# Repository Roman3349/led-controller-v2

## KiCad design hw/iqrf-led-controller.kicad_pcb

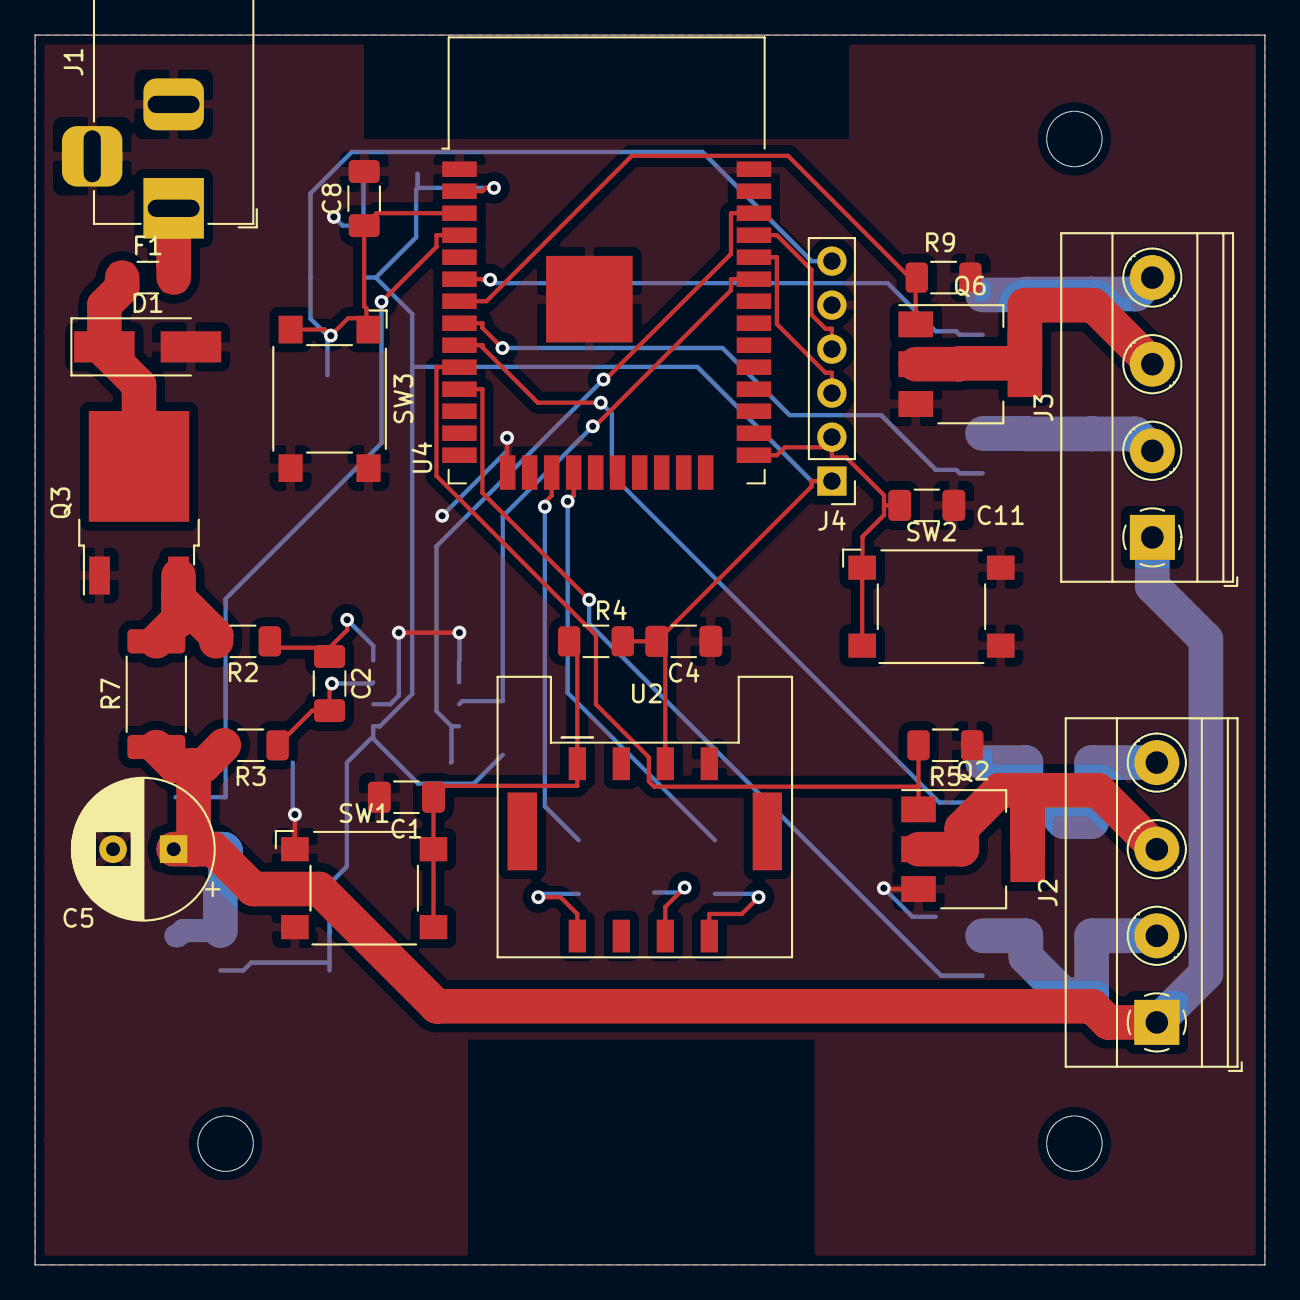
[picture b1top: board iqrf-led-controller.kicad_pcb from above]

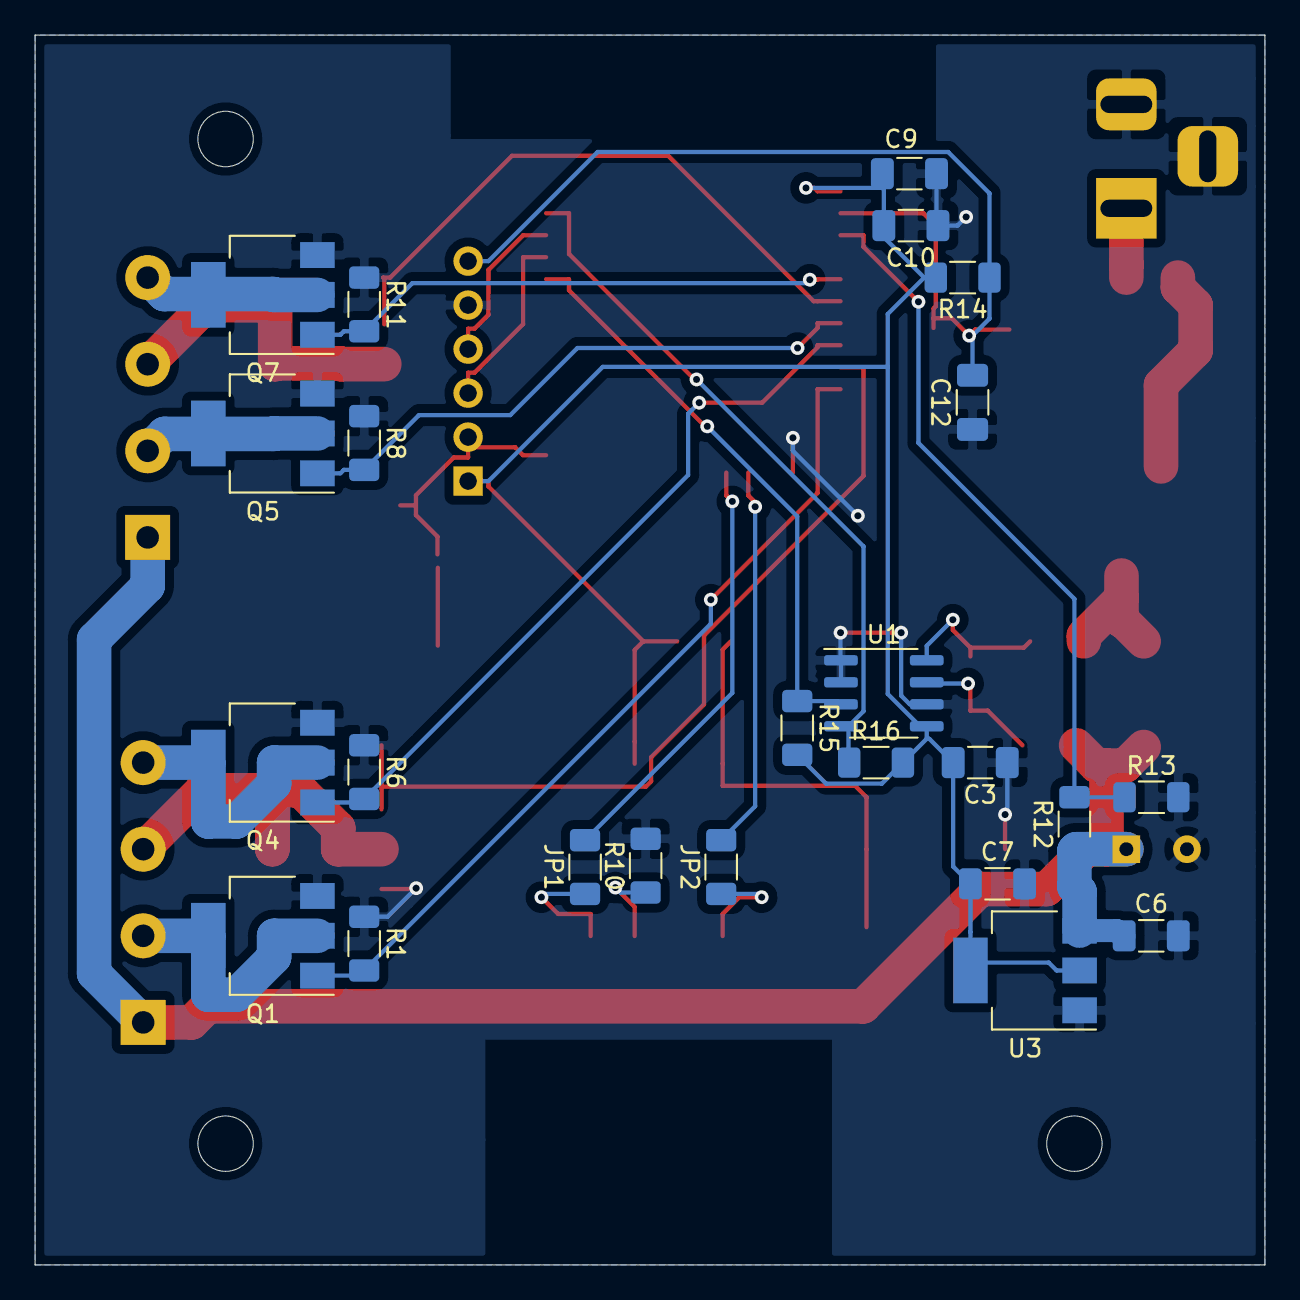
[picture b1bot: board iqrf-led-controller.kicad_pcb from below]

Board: 2 copper layers, 71.0 x 71.0 mm, 53 parts (24 on the bottom side), 33 nets.

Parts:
C1, C2, C3, C4, C8, C10, C11, C12: 100n; C_1206_3216Metric_Pad1.33x1.80mm_HandSolder
C5: 470u; CP_Radial_D8.0mm_P3.50mm
C6: 1u; C_1206_3216Metric_Pad1.33x1.80mm_HandSolder
C7: 4.7u; C_1206_3216Metric_Pad1.33x1.80mm_HandSolder
C9: 22u; C_1206_3216Metric_Pad1.33x1.80mm_HandSolder
D1: SMAJ12CA-E3/61; D_SMA_Handsoldering
F1: 2A; Fuse_1206_3216Metric_Pad1.42x1.75mm_HandSolder
H1, H2, H3: MountingHole; MountingHole_3.2mm_M3
J1: Barrel_Jack_Switch; BarrelJack_Horizontal
J2, J3: DG300-5.0; TerminalBlock_Phoenix_MKDS-1,5-4_1x04_P5.00mm_Horizontal
J4: Conn_01x06; PinHeader_1x06_P2.54mm_Vertical
JP1, JP2: Jumper_2_Bridged; R_1206_3216Metric_Pad1.30x1.75mm_HandSolder
Q1, Q2, Q4, Q5, Q6, Q7: BUK98150-55A; SOT-223-3_TabPin2
Q3: FDD4243; TO-252-2
R1, R4, R5, R6, R8, R9, R11, R12, R14: 10k; R_1206_3216Metric_Pad1.30x1.75mm_HandSolder
R2, R3: 10R; R_1206_3216Metric_Pad1.30x1.75mm_HandSolder
R7: R100; R_2512_6332Metric_Pad1.40x3.35mm_HandSolder
R10: 4.7k; R_1206_3216Metric_Pad1.30x1.75mm_HandSolder
R13: 2.7k; R_1206_3216Metric_Pad1.30x1.75mm_HandSolder
R15, R16: 3.3k; R_1206_3216Metric_Pad1.30x1.75mm_HandSolder
SW1, SW2, SW3: SW_Push_Dual; SW_SPST_Omron_B3FS-100xP
U1: INA219AxD; SOIC-8_3.9x4.9mm_P1.27mm
U2: TR-72DAT; IQRF_TRx2DA_KON-SIM-01
U3: LDL1117S33R_SOT223; SOT-223-3_TabPin2
U4: ESP32-WROOM-32D; ESP32-WROOM-32

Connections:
+3V3: C3.2, C4.2, C7.1, C9.2, C10.2, J4.1, R4.2, R14.2, R15.2, R16.2, U1.5, U2.C3, U3.2, U4.2
ESP32_EN: C8.1, C12.2, J4.6, R14.1, SW3.1, SW3.3, U4.3
GND: C1.2, C3.1, C4.1, C5.2, C6.2, C7.2, C8.2, C9.1, C10.1, C11.1, C12.1, D1.2, J1.2, J1.3, J4.5, Q1.3, Q2.3, Q3.1, Q4.3, Q5.3, Q6.3, Q7.3, R1.1, R5.1, R6.1, R8.1, R9.1, R10.2, R11.1, R13.2, SW1.1, SW1.3, SW2.2, SW2.4, SW3.2, SW3.4, U1.1, U1.2, U1.6, U2.C4, U3.1, U4.1, U4.15, U4.38, U4.39
GPIO0: C11.2, J4.2, SW2.1, SW2.3, U4.25
IQRF_RX: JP1.1, U2.C8
IQRF_TX: JP2.1, U2.C5
unnamed: C1.1, R4.1, SW1.2, SW1.4, U2.C1
unnamed: C2.1, R2.1, U1.8
unnamed: C2.2, R3.1, U1.7
unnamed: D1.1, F1.1, Q3.2
unnamed: F1.2, J1.1
unnamed: J2.2, Q1.2
unnamed: J2.3, Q2.2
unnamed: J2.4, Q4.2
unnamed: J3.2, Q5.2
unnamed: J3.3, Q6.2
unnamed: J3.4, Q7.2
unnamed: R10.1, U2.C7
unnamed: R12.2, R13.1, U4.4
PWM1: Q1.1, R1.2, U4.11
PWM2: Q2.1, R5.2, U4.10
PWM3: Q4.1, R6.2, U4.9
PWM4: Q5.1, R8.2, U4.8
PWM5: Q6.1, R9.2, U4.7
PWM6: Q7.1, R11.2, U4.6
SCL: R16.1, U1.4, U4.36
SDA: R15.1, U1.3, U4.33
SHUNT+: Q3.3, R2.2, R7.2
SHUNT-: C5.1, C6.1, J2.1, J3.1, R3.2, R7.1, R12.1, U3.3
UART0_RX: J4.3, U4.34
UART0_TX: J4.4, U4.35
UART1_RX: JP2.2, U4.17
UART1_TX: JP1.2, U4.18

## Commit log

2020-12-20 ESP32: add basic UART functionality
2020-12-20 HW: add KiCAD project
2020-12-20 IQRF: add Custom DPA handler
2020-12-20 Docs: add basic docs
2020-12-26 ESP32: implement GATT services and characteristics for device info and lights
2020-12-26 ESP32: fix GATTS services
2020-12-27 ESP32: add INA219
2020-12-27 IQRF: add IQRF Standard Sensors
2020-12-28 ESP32: improve IQRF component
2020-12-28 IQRF: clean RX buffer
2020-12-28 ESP32: fix formats
2021-01-11 Docs: add more info
